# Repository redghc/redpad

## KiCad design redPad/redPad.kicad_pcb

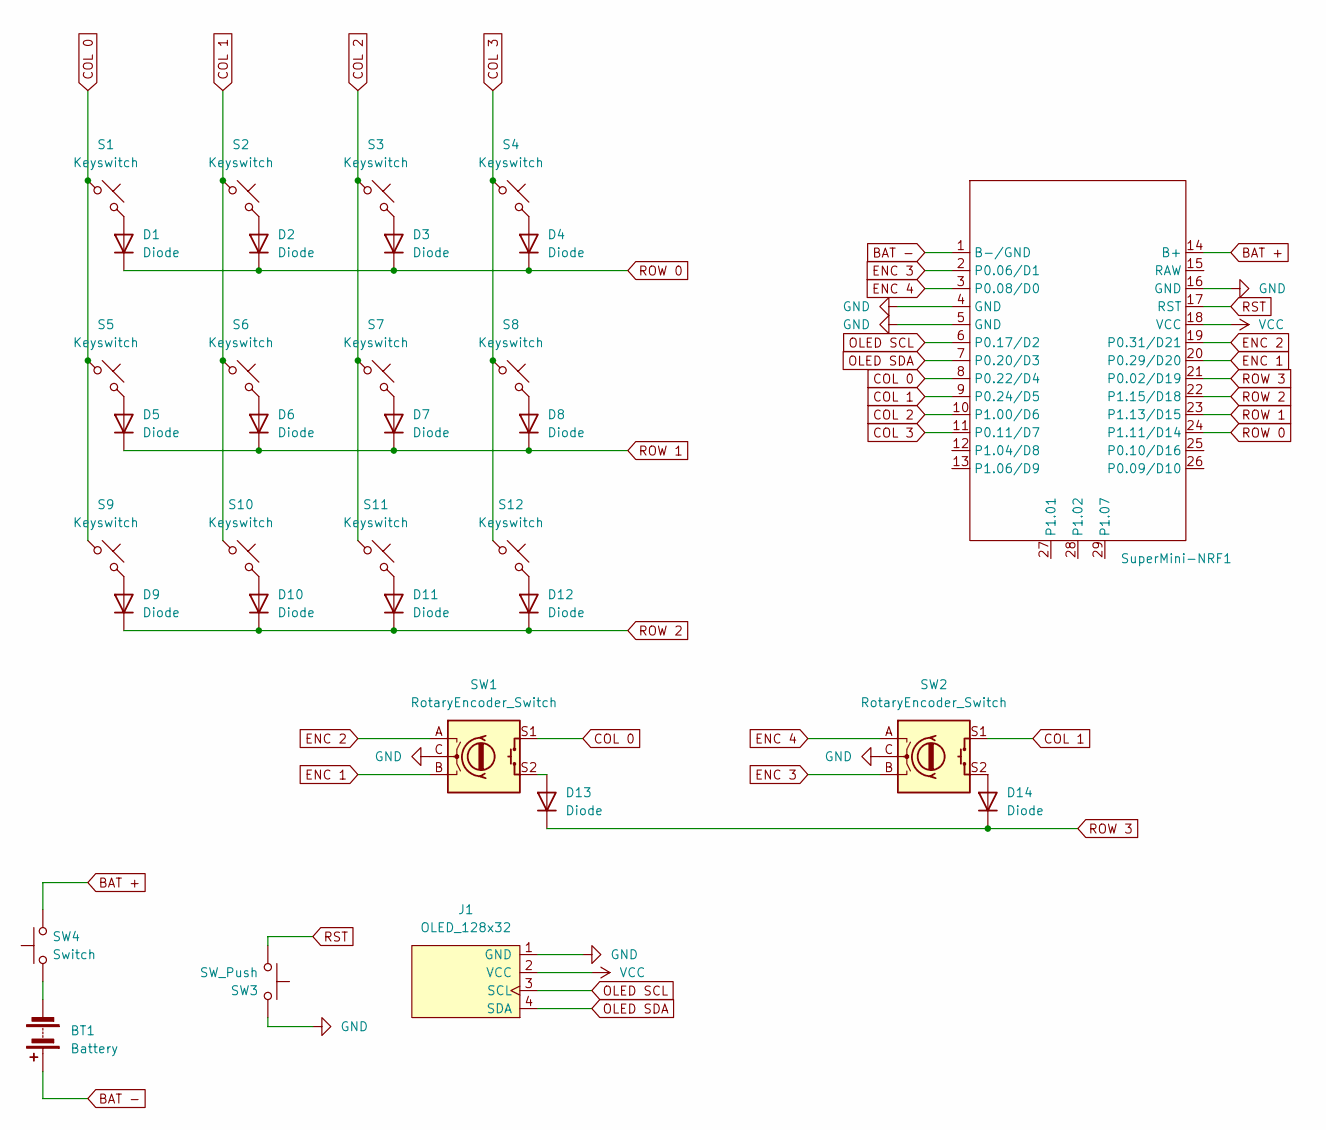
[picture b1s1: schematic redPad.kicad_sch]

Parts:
BT1: Battery; JST_EH_S2B-EH_1x02_P2.50mm_Horizontal
D1, D2, D3, D4, D5, D6, D7, D8, D9, D10, D11, D12, D13, D14: Diode; D_SOD-123
J1: OLED_128x32
S1, S2, S3, S4, S5, S6, S7, S8, S9, S10, S11, S12: Keyswitch; Hotswap_MX_1.00u
SW1, SW2: RotaryEncoder_Switch; RotaryEncoder_Alps_EC11E-Switch_Vertical_H20mm
SW3: SW_Push; SW TS-B003-Y
SW4: Switch; Switch_MSK12C02
SuperMini-NRF1: SuperMini NRF52840

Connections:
BAT +: SW4.2, SuperMini-NRF1.14 (B+)
BAT -: BT1.1 (+), SuperMini-NRF1.1 (B-/GND)
COL 0: S1.1, S5.1, S9.1, SW1.S1, SuperMini-NRF1.8 (P0.22/D4)
COL 1: S2.1, S6.1, S10.1, SW2.S1, SuperMini-NRF1.9 (P0.24/D5)
COL 2: S3.1, S7.1, S11.1, SuperMini-NRF1.10 (P1.00/D6)
COL 3: S4.1, S8.1, S12.1, SuperMini-NRF1.11 (P0.11/D7)
ENC 1: SW1.B, SuperMini-NRF1.20 (P0.29/D20)
ENC 2: SW1.A, SuperMini-NRF1.19 (P0.31/D21)
ENC 3: SW2.B, SuperMini-NRF1.2 (P0.06/D1)
ENC 4: SW2.A, SuperMini-NRF1.3 (P0.08/D0)
GND: J1.1 (GND), SW1.C, SW2.C, SW3.2, SuperMini-NRF1.4 (GND), SuperMini-NRF1.5 (GND), SuperMini-NRF1.16 (GND)
unnamed: BT1.2 (-), SW4.1
unnamed: D1.2 (A), S1.2
unnamed: D2.2 (A), S2.2
unnamed: D3.2 (A), S3.2
unnamed: D4.2 (A), S4.2
unnamed: D5.2 (A), S5.2
unnamed: D6.2 (A), S6.2
unnamed: D7.2 (A), S7.2
unnamed: D8.2 (A), S8.2
unnamed: D9.2 (A), S9.2
unnamed: D10.2 (A), S10.2
unnamed: D11.2 (A), S11.2
unnamed: D12.2 (A), S12.2
unnamed: D13.2 (A), SW1.S2
unnamed: D14.2 (A), SW2.S2
OLED SCL: J1.3 (SCL), SuperMini-NRF1.6 (P0.17/D2)
OLED SDA: J1.4 (SDA), SuperMini-NRF1.7 (P0.20/D3)
ROW 0: D1.1 (K), D2.1 (K), D3.1 (K), D4.1 (K), SuperMini-NRF1.24 (P1.11/D14)
ROW 1: D5.1 (K), D6.1 (K), D7.1 (K), D8.1 (K), SuperMini-NRF1.23 (P1.13/D15)
ROW 2: D9.1 (K), D10.1 (K), D11.1 (K), D12.1 (K), SuperMini-NRF1.22 (P1.15/D18)
ROW 3: D13.1 (K), D14.1 (K), SuperMini-NRF1.21 (P0.02/D19)
RST: SW3.1, SuperMini-NRF1.17 (RST)
VCC: J1.2 (VCC), SuperMini-NRF1.18 (VCC)

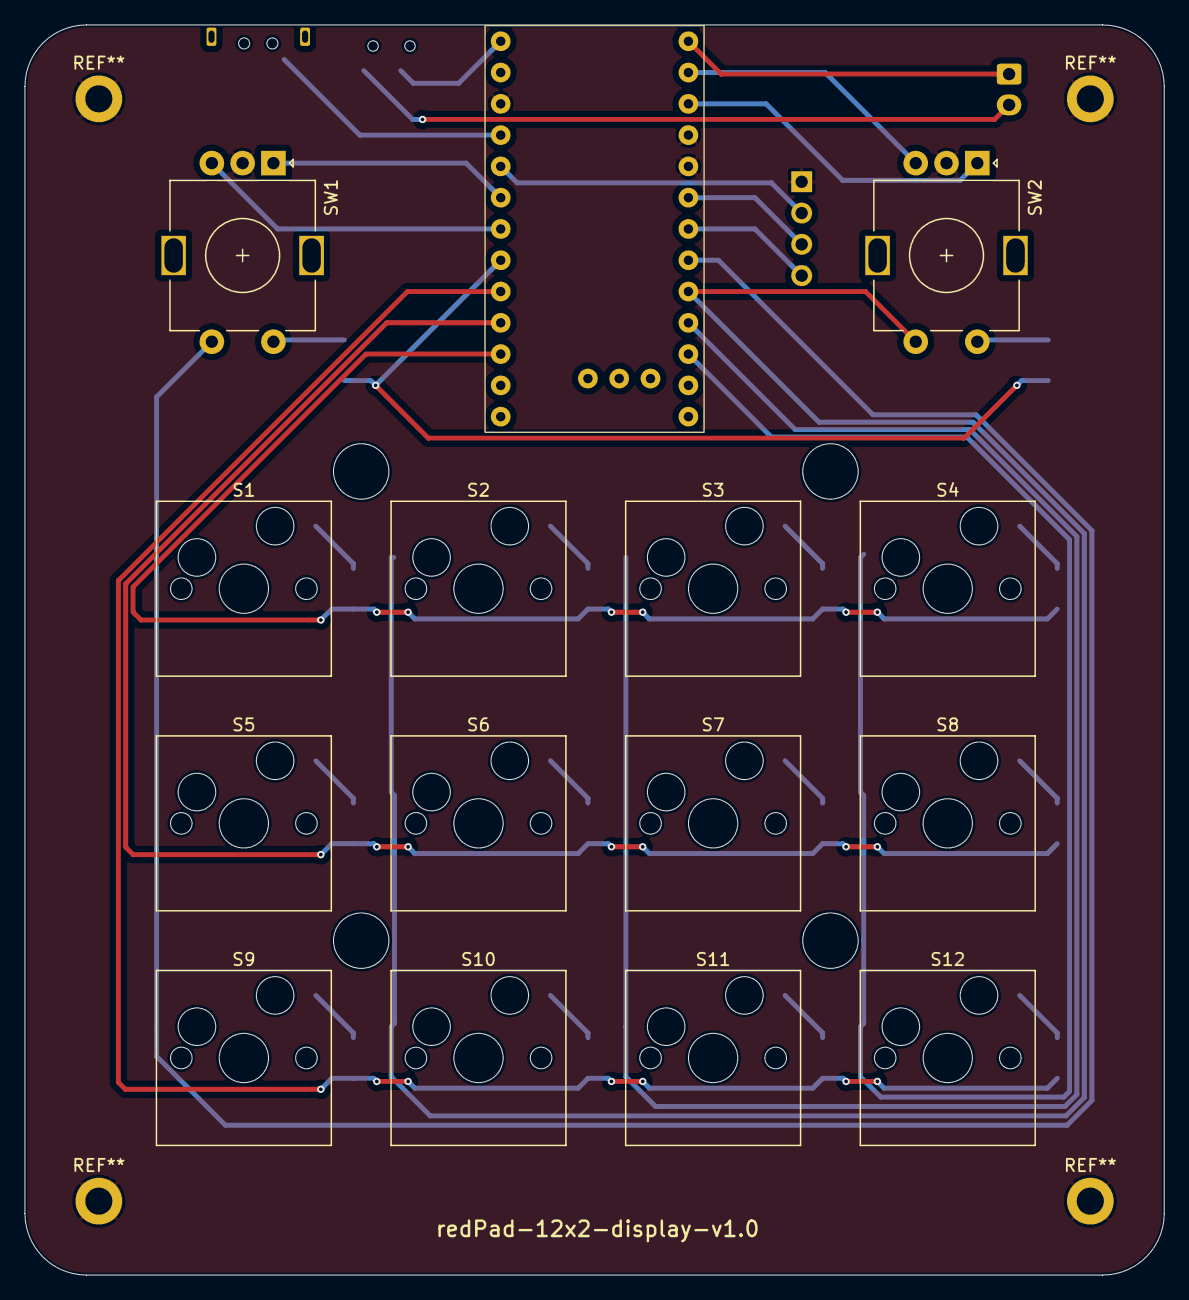
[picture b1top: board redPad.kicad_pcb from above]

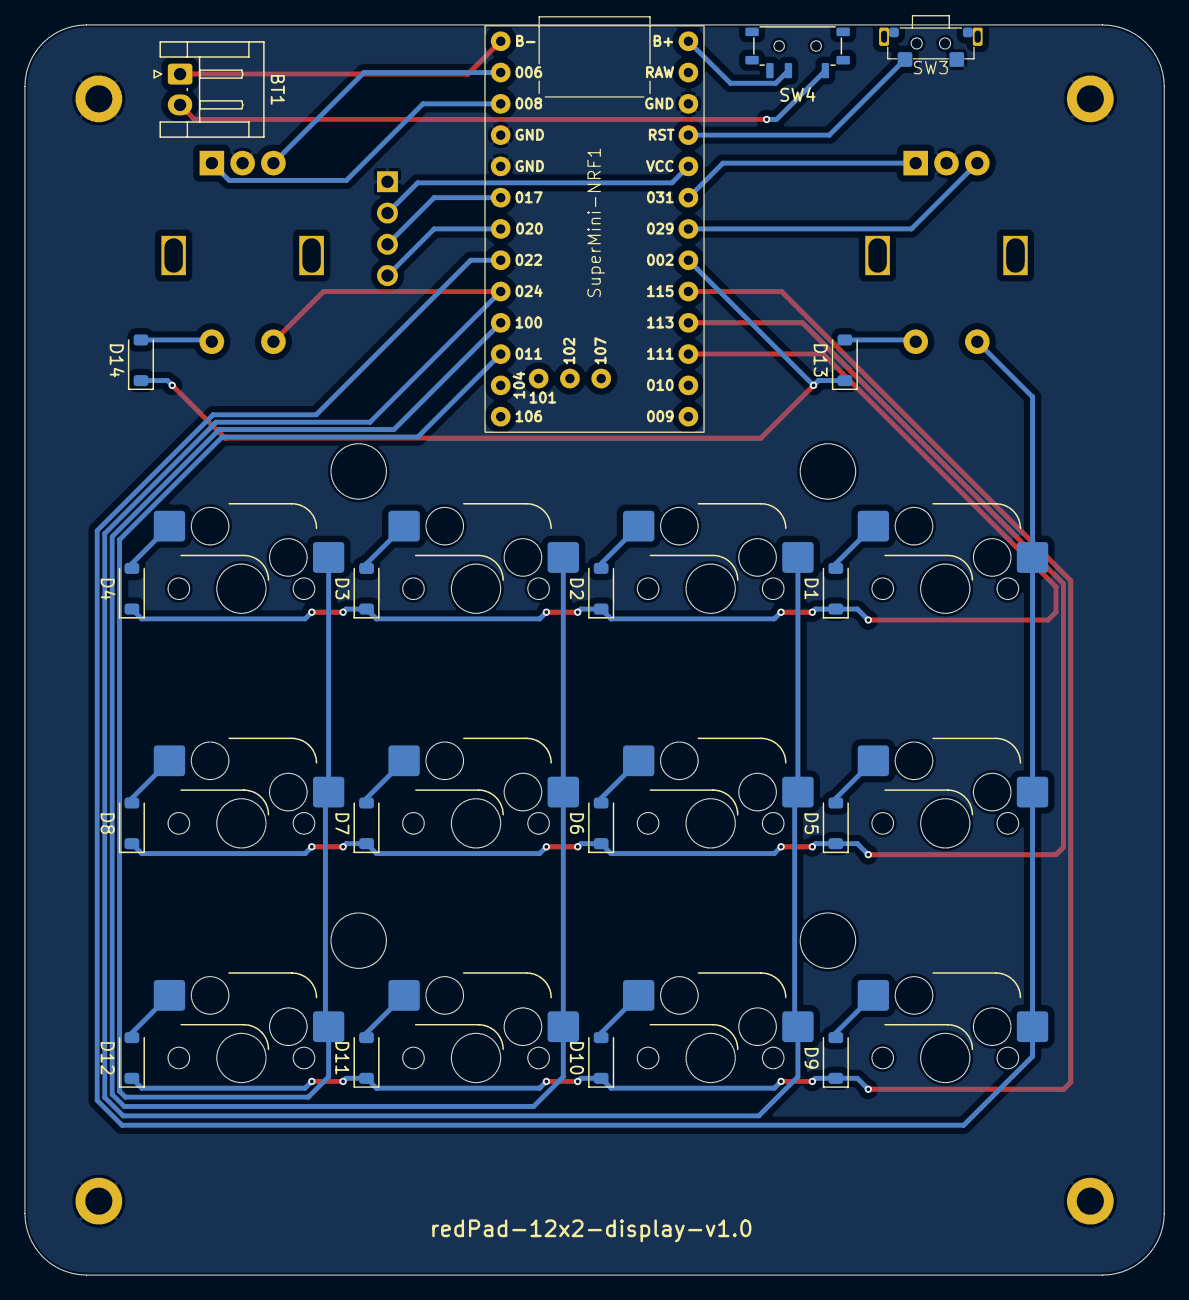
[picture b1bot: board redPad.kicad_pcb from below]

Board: 2 copper layers, 92.5 x 101.5 mm, 33 parts (18 on the bottom side), 34 nets.

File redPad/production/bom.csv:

Designator,Footprint,Quantity,Value,LCSC Part #
BT1,JST_EH_S2B-EH_1x02_P2.50mm_Horizontal,1,Battery,
"D1, D10, D11, D12, D13, D14, D2, D3, D4, D5, D6, D7, D8, D9",D_SOD-123,14,Diode,
J1,OLED_128x32,1,OLED_128x32,
"S1, S10, S11, S12, S2, S3, S4, S5, S6, S7, S8, S9",Hotswap_MX_1.00u,12,Keyswitch,
SUPERMINI-NRF1,SuperMini NRF52840,1,~,
"SW1, SW2",RotaryEncoder_Alps_EC11E-Switch_Vertical_H20mm,2,RotaryEncoder_Switch,
SW3,SW TS-B003-Y,1,SW_Push,
SW4,Switch_MSK12C02,1,Switch,

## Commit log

2025-04-16 Start of project
2025-04-17 Avance en teclado
2025-04-17 Version 1.0 finalizada
